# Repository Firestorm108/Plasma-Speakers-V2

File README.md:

# Plasma-Speakers-V2

Dual flyback transformers that produce audio through the modulation of high frequency plasma arcs.

# What is it?
This is version two of my plasma speaker project (https://github.com/Firestorm108/Stereo-Plasma-Speaker). It produces arcs much larger than the previous version, and the heating of the MOSFETs is much lower. This is because it sort of combines two types of oscillating technologies. It uses the same principle of a ZVS driver, switching at zero volts for a great efficiency, but it is able to do this digitally instead of through analog components.

# Images

| Item                     |    Price | Link                                                                                                     |
| ------------------------ | -------: | -------------------------------------------------------------------------------------------------------- |
| PCB + Assembly           |     $170 | JLCPCB                                                                                                   |
| IRFP460 MOSFETs          |      $12 | [Amazon](https://www.amazon.com/ACEIRMC-Transistors-IRFP260N-N-Channel-IRFP260NPBF/dp/B0CGHP2LH6)        |
| AC Cable                 |       $7 | [Amazon](https://www.amazon.com/Standard-Electronics-Computer-Printer-Monitor/dp/B09VRLJD7J/)            |
| 25A 24V PSU              |      N/A | Already Owned                                                                                            |
| Flyback Transformers (2) |      $50 | [Amazon](https://www.amazon.com/TEAMWILL-Transformer-BSC24-39202-BSC26-N2137-BSC26-N2138/dp/B09P2Y9X9F/) |
| **Total**                | **$239** |                                                                                                          |

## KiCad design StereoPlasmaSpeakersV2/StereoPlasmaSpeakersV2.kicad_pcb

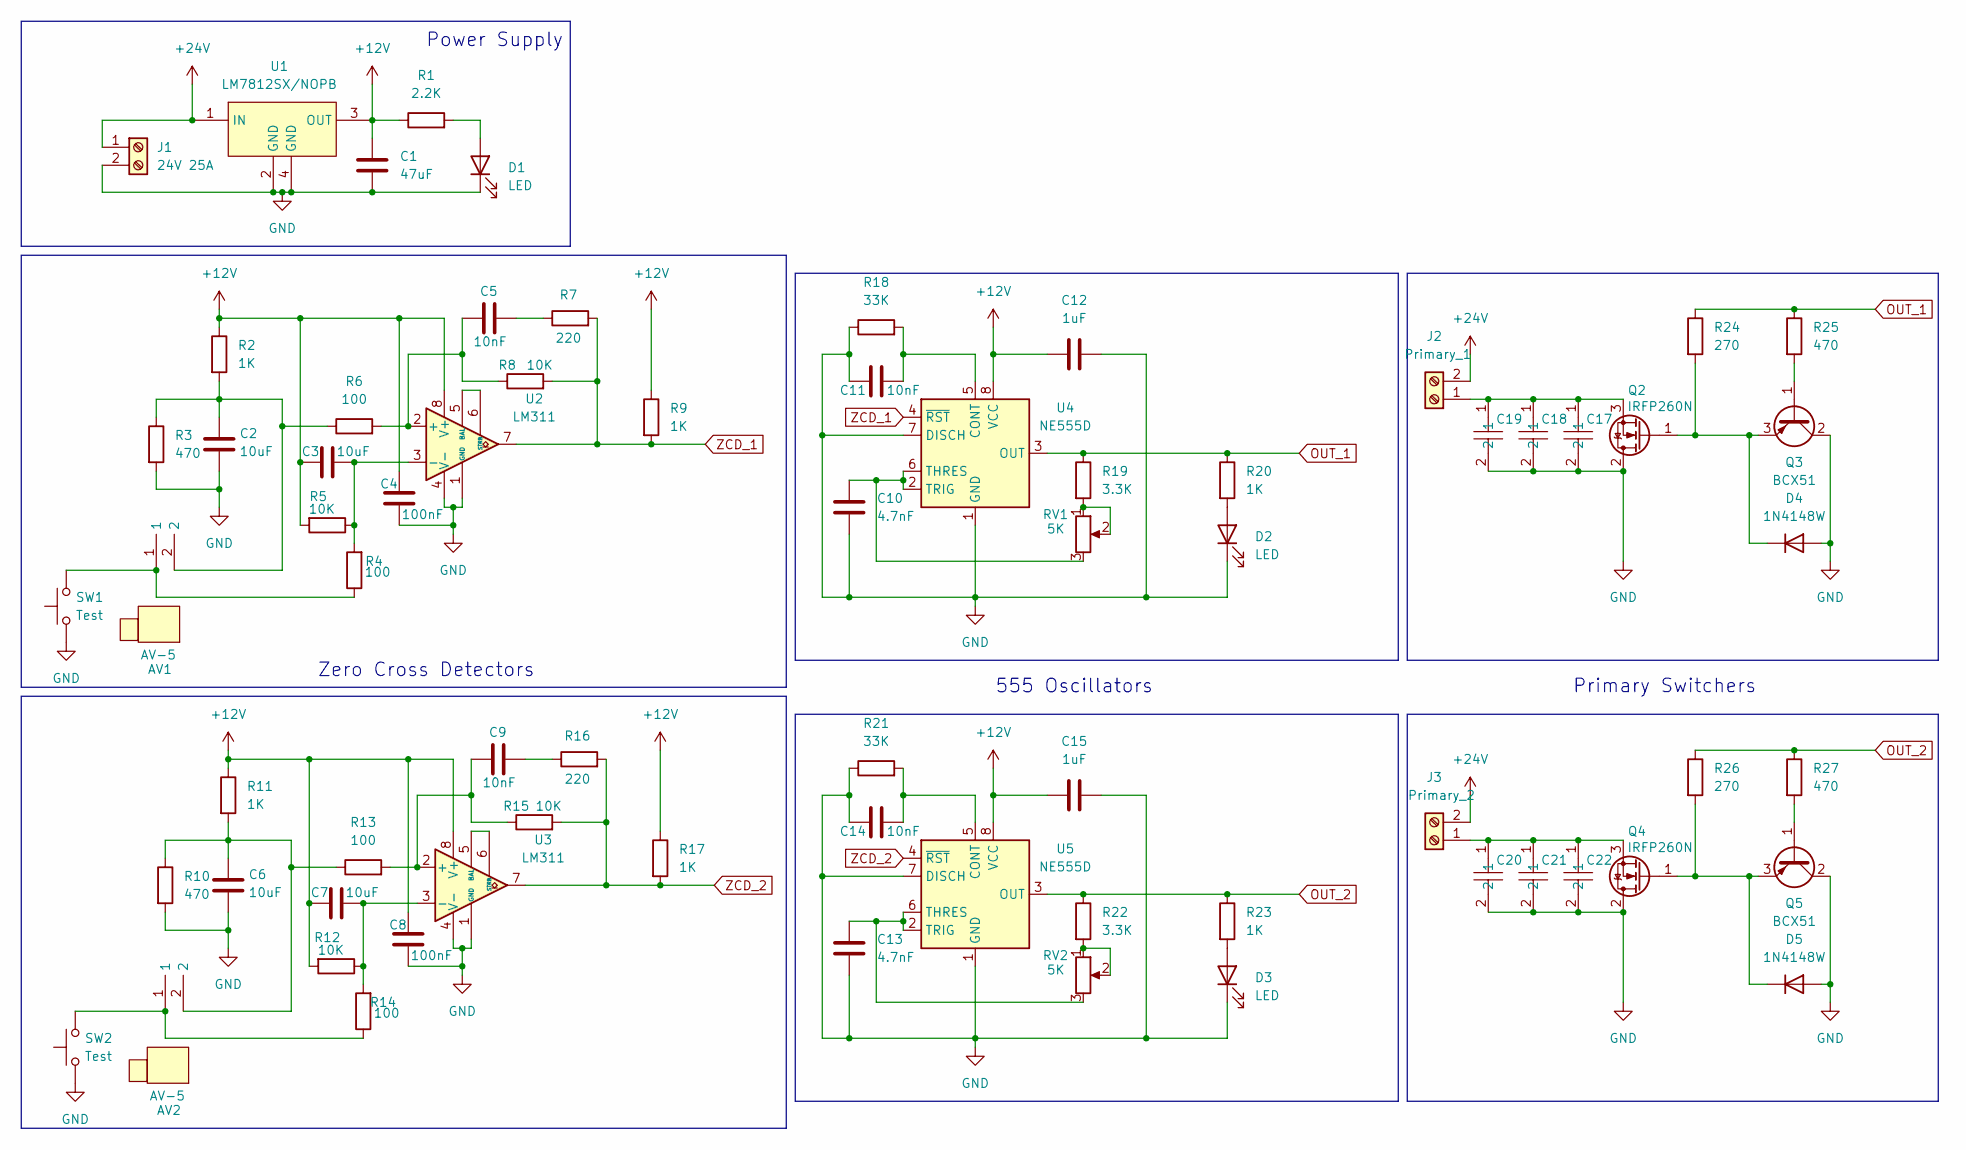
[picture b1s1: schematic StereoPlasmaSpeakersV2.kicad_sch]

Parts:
AV1, AV2: AV-5; CONN-TH_AV-5; MPN AV-5; LCSC Part C18080
C1: 47uF; C_1206_3216Metric
C2, C3, C6, C7: 10uF; C_1206_3216Metric
C4, C8: 100nF; C_1206_3216Metric
C5, C9, C11, C14: 10nF; C_1206_3216Metric
C10, C13: 4.7nF; C_1206_3216Metric
C12, C15: 1uF; C_1206_3216Metric
C17, C18, C19, C20, C21, C22: C322J10458P40001; CAP-TH_L12.0-W6.0-P10.00-D0.6-A; MPN C322J10458P40001; LCSC Part C46638903
D1, D2, D3: LED; LED_1206_3216Metric
D4, D5: 1N4148W; D_SOD-123
J1: 24V 25A; CONN-TH_P10.16_KF135T-10.16-2P
J2: Primary_1; CONN-TH_P10.16_KF135T-10.16-2P
J3: Primary_2; CONN-TH_P10.16_KF135T-10.16-2P
Q2, Q4: IRFP260N; TO-247-3_Vertical
Q3, Q5: BCX51; SOT-89-3
R1: 2.2K; R_1206_3216Metric
R2, R9, R11, R17, R20, R23: 1K; R_1206_3216Metric
R3, R10, R25, R27: 470; R_1206_3216Metric
R4, R6, R13, R14: 100; R_1206_3216Metric
R5, R8, R12, R15: 10K; R_1206_3216Metric
R7, R16: 220; R_1206_3216Metric
R18, R21: 33K; R_1206_3216Metric
R19, R22: 3.3K; R_1206_3216Metric
R24, R26: 270; R_1206_3216Metric
RV1, RV2: 5K; RES-ADJ-TH_3296W
SW1, SW2: Test; SW_Push_SPST_NO_Alps_SKRK
U1: LM7812SX/NOPB; TO-263-3_L8.6-W10.2-P2.54-LS14.4-BR; MPN LM7812SX/NOPB; LCSC Part C2870248
U2, U3: LM311; SOIC-8_L5.0-W4.0-P1.27-LS6.0-BL
U4, U5: NE555D; SOIC-8_3.9x4.9mm_P1.27mm

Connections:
+12V: C1.1, C3.1, C4.1, C7.1, C8.1, C12.2, C15.2, R1.1, R2.1, R5.2, R9.1, R11.1, R12.2, R17.1, U1.3 (OUT), U2.8 (V+), U3.8 (V+), U4.8 (VCC), U5.8 (VCC)
+24V: J1.1, J2.2, J3.2, U1.1 (IN)
GND: C1.2, C2.2, C4.2, C6.2, C8.2, C10.2, C11.1, C12.1, C13.2, C14.1, C15.1, C17.2, C18.2, C19.2, C20.2, C21.2, C22.2, D1.1 (K), D2.1 (K), D3.1 (K), D4.2 (A), D5.2 (A), J1.2, Q2.2 (D), Q3.2 (C), Q4.2 (D), Q5.2 (C), R3.2, R10.2, R18.1, R21.1, SW1.1, SW2.1, U1.2 (GND), U1.4 (GND), U2.1 (GND), U2.4 (V-), U3.1 (GND), U3.4 (V-), U4.1 (GND), U4.7 (DISCH), U5.1 (GND), U5.7 (DISCH)
unnamed: AV1.1, R4.1, SW1.2
unnamed: AV1.2, C2.1, R2.2, R3.1, R6.1
unnamed: AV2.1, R14.1, SW2.2
unnamed: AV2.2, C6.1, R10.1, R11.2, R13.1
unnamed: C5.2, R7.1
unnamed: C9.2, R16.1
unnamed: D1.2 (A), R1.2
unnamed: D2.2 (A), R20.2
unnamed: D3.2 (A), R23.2
unnamed: D4.1 (K), Q2.1 (G), Q3.3 (E), R24.2
unnamed: D5.1 (K), Q4.1 (G), Q5.3 (E), R26.2
unnamed: C17.1, C18.1, C19.1, J2.1, Q2.3 (S)
unnamed: C20.1, C21.1, C22.1, J3.1, Q4.3 (S)
unnamed: Q3.1 (B), R25.2
unnamed: Q5.1 (B), R27.2
unnamed: R19.2, RV1.1, RV1.2
unnamed: R22.2, RV2.1, RV2.2
unnamed: C5.1, R6.2, R8.1, U2.2 (+)
unnamed: C3.2, R4.2, R5.1, U2.3 (-)
unnamed: U2.5 (BAL), U2.6 (STRB)
unnamed: C9.1, R13.2, R15.1, U3.2 (+)
unnamed: C7.2, R12.1, R14.2, U3.3 (-)
unnamed: U3.5 (BAL), U3.6 (STRB)
unnamed: C11.2, R18.2, U4.5 (CONT)
unnamed: C10.1, RV1.3, U4.2 (TRIG), U4.6 (THRES)
unnamed: C14.2, R21.2, U5.5 (CONT)
unnamed: C13.1, RV2.3, U5.2 (TRIG), U5.6 (THRES)
OUT_1: R19.1, R20.1, R24.1, R25.1, U4.3 (OUT)
OUT_2: R22.1, R23.1, R26.1, R27.1, U5.3 (OUT)
ZCD_1: R7.2, R8.2, R9.2, U2.7, U4.4 (~RST)
ZCD_2: R15.2, R16.2, R17.2, U3.7, U5.4 (~RST)

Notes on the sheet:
Power Supply
Primary Switchers
Zero Cross Detectors
555 Oscillators

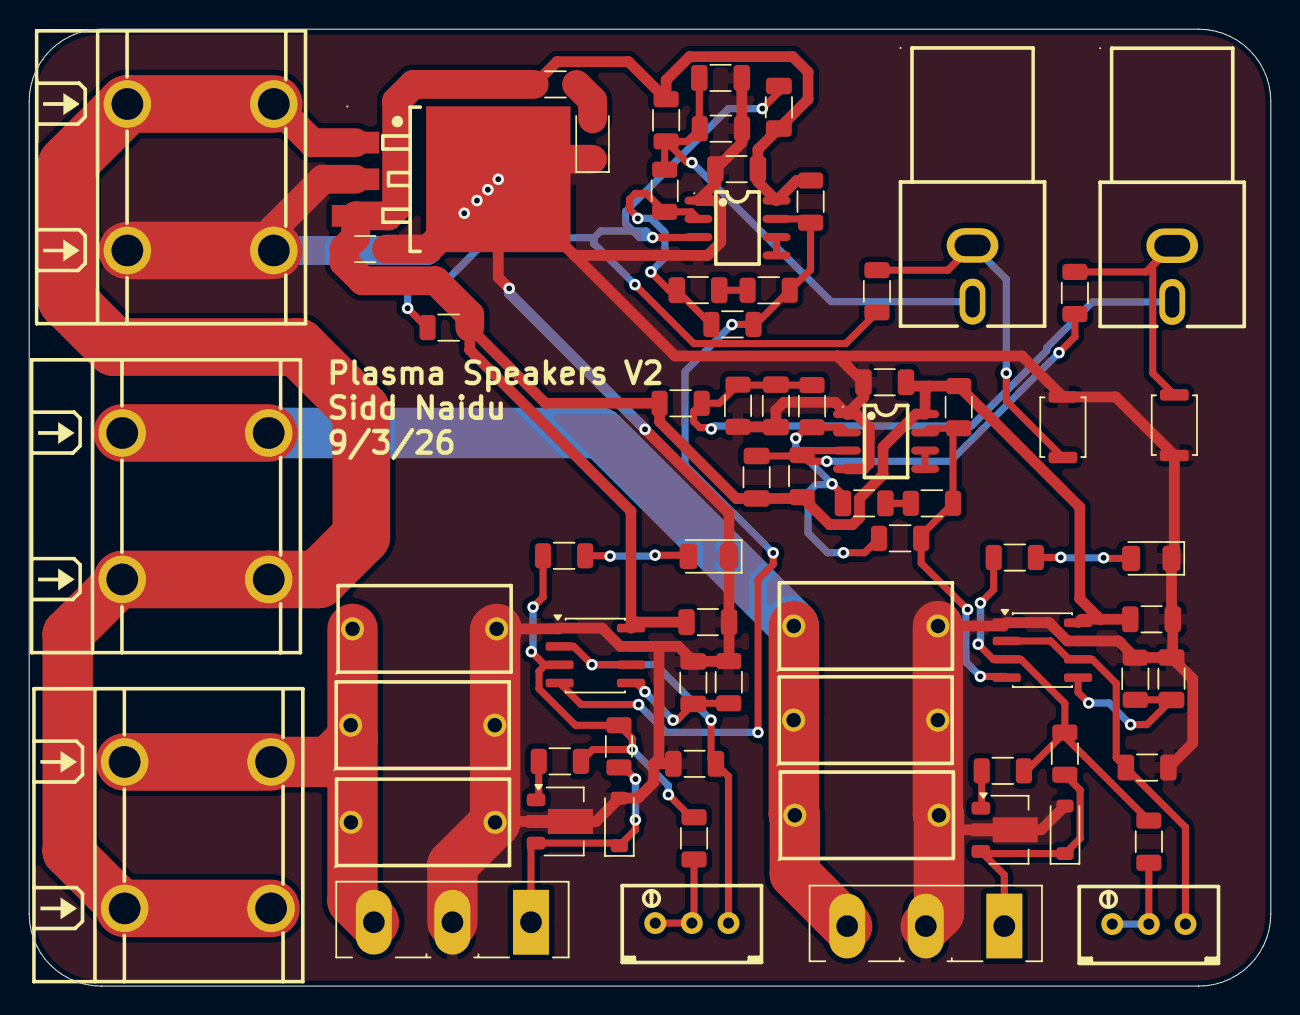
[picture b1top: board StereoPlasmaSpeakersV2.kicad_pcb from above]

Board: 2 copper layers, 86.1 x 66.4 mm, 71 parts (0 on the bottom side), 34 nets.

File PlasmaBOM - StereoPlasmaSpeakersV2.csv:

Id,Designator,Footprint,Quantity,Comment,Supplier and ref
1,"AV1, AV2",CONN-TH_AV-5,2,AV-5,
2,C1,C_1206_3216Metric,1,47uF,
3,"C2, C3, C6, C7",C_1206_3216Metric,4,10uF,
4,"C4, C8",C_1206_3216Metric,2,100nF,
5,"C5, C9, C11, C14",C_1206_3216Metric,4,10nF,
6,"C10, C13",C_1206_3216Metric,2,4.7nF,
7,"C12, C15",C_1206_3216Metric,2,1uF,
8,"C17, C18, C19, C20, C21, C22",CAP-TH_L12.0-W6.0-P10.00-D0.6-A,6,C322J10458P40001,
9,"D1, D2, D3",LED_1206_3216Metric,3,LED,
10,"D4, D5",D_SOD-123,2,1N4148W,
11,J1,CONN-TH_P10.16_KF135T-10.16-2P,1,24V 25A,
12,J2,CONN-TH_P10.16_KF135T-10.16-2P,1,Primary_1,
13,J3,CONN-TH_P10.16_KF135T-10.16-2P,1,Primary_2,
14,"Q2, Q4",TO-247-3_Vertical,2,IRFP260N,
15,"Q3, Q5",SOT-89-3,2,BCX51,
16,R1,R_1206_3216Metric,1,2.2K,
17,"R2, R9, R11, R17, R20, R23",R_1206_3216Metric,6,1K,
18,"R3, R10, R25, R27",R_1206_3216Metric,4,470,
19,"R4, R6, R13, R14",R_1206_3216Metric,4,100,
20,"R5, R8, R12, R15",R_1206_3216Metric,4,10K,
21,"R7, R16",R_1206_3216Metric,2,220,
22,"R18, R21",R_1206_3216Metric,2,33K,
23,"R19, R22",R_1206_3216Metric,2,3.3K,
24,"R24, R26",R_1206_3216Metric,2,270,
25,"RV1, RV2",RES-ADJ-TH_3296W,2,5K,
26,"SW1, SW2",SW_Push_SPST_NO_Alps_SKRK,2,Test,
27,U1,TO-263-3_L8.6-W10.2-P2.54-LS14.4-BR,1,LM7812SX/NOPB,
28,"U2, U3",SOIC-8_L5.0-W4.0-P1.27-LS6.0-BL,2,LM311,
29,"U4, U5",SOIC-8_3.9x4.9mm_P1.27mm,2,NE555D,
